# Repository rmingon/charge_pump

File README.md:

# Ultra tiny 3.3V or 2.5V Step-Up/Step-Down Charge Pump DC/DC Converter for IOT based on LTC3240

## Thank you to [PCBWay](https://www.pcbway.com/) for sponsoring the PCB production of this prototype.

### This project exist for use IOT device with Alcaline/LIPO battery

### PCBWAY WORK

### FINISH PROJECT

## This device can give 3.3V with 1.8V to 5.5v input without self (see below)

> **Warning** Between 1.8v and 2.5v in input the LTC3240 can give only 40mA

- - - -

#### SCHEMATIC VIEW

#### PCB VIEW

#### 3D VIEW FRONT

#### 3D VIEW BACK

Thank you to [PCBWay](https://www.pcbway.com/) for sponsoring this project by covering the cost of PCB production for beta. The boards turned out very nicely. The green solder mask looks solid and the grills holes is perfect.

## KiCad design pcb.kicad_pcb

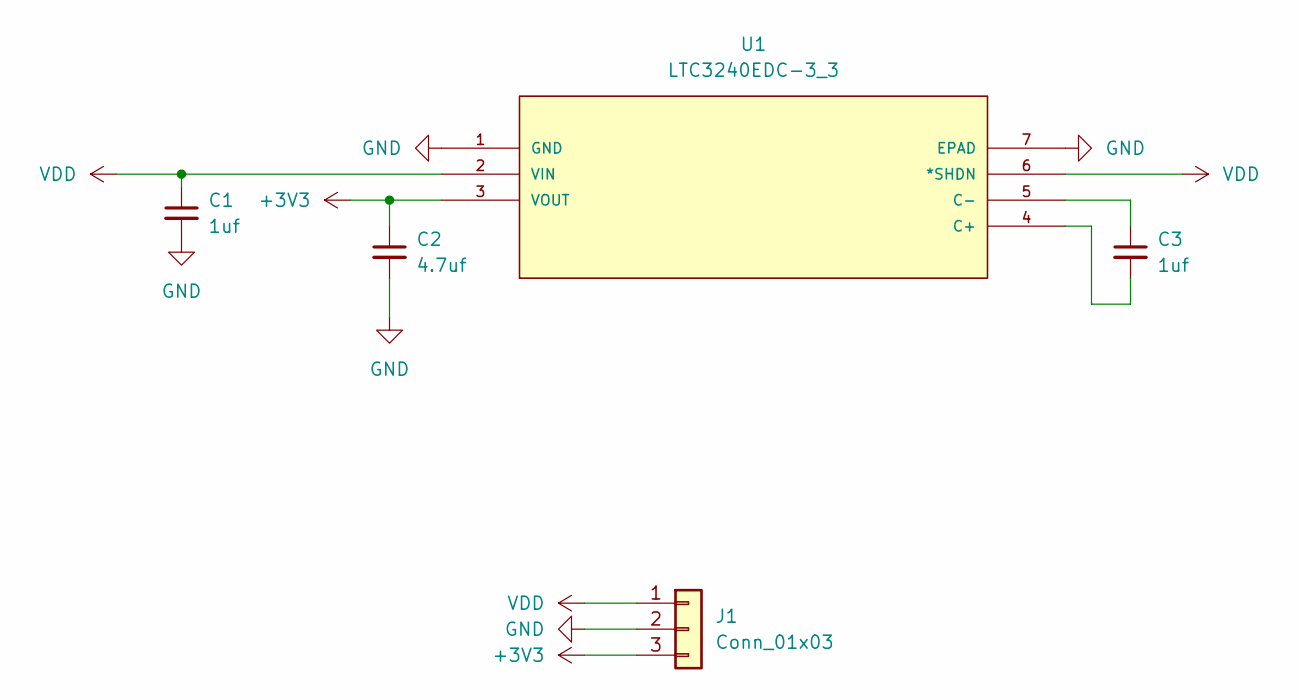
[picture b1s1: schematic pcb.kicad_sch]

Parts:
C1, C3: 1uf; C_0603_1608Metric
C2: 4.7uf; C_0603_1608Metric
J1: Conn_01x03; PinHeader_1x03_P2.54mm_Vertical
U1: LTC3240EDC-3_3; DFN-6-1EP_2x2mm_P0.5mm_EP0.61x1.42mm; MANUFACTURER_PART_NUMBER ltc3240edc3.3

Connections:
+3V3: C2.1, J1.3, U1.3 (VOUT)
GND: C1.2, C2.2, J1.2, U1.1 (GND), U1.7 (EPAD)
unnamed: C3.2, U1.4 (C+)
unnamed: C3.1, U1.5 (C-)
VDD: C1.1, J1.1, U1.2 (VIN), U1.6 (*SHDN)

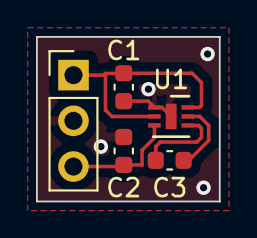
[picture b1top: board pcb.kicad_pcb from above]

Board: 2 copper layers, 10.2 x 9.1 mm, 5 parts (0 on the bottom side), 5 nets.

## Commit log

2023-08-22 add ltc3240
2023-08-22 add header
2023-08-22 add pcb wiring
2023-08-22 add pcb text
2023-08-22 add picture
2023-08-22 update pcb + schematic
2023-08-22 add datasheet
2023-08-22 add readme
2023-08-22 fix readme
2023-09-13 add pcbway sponso
